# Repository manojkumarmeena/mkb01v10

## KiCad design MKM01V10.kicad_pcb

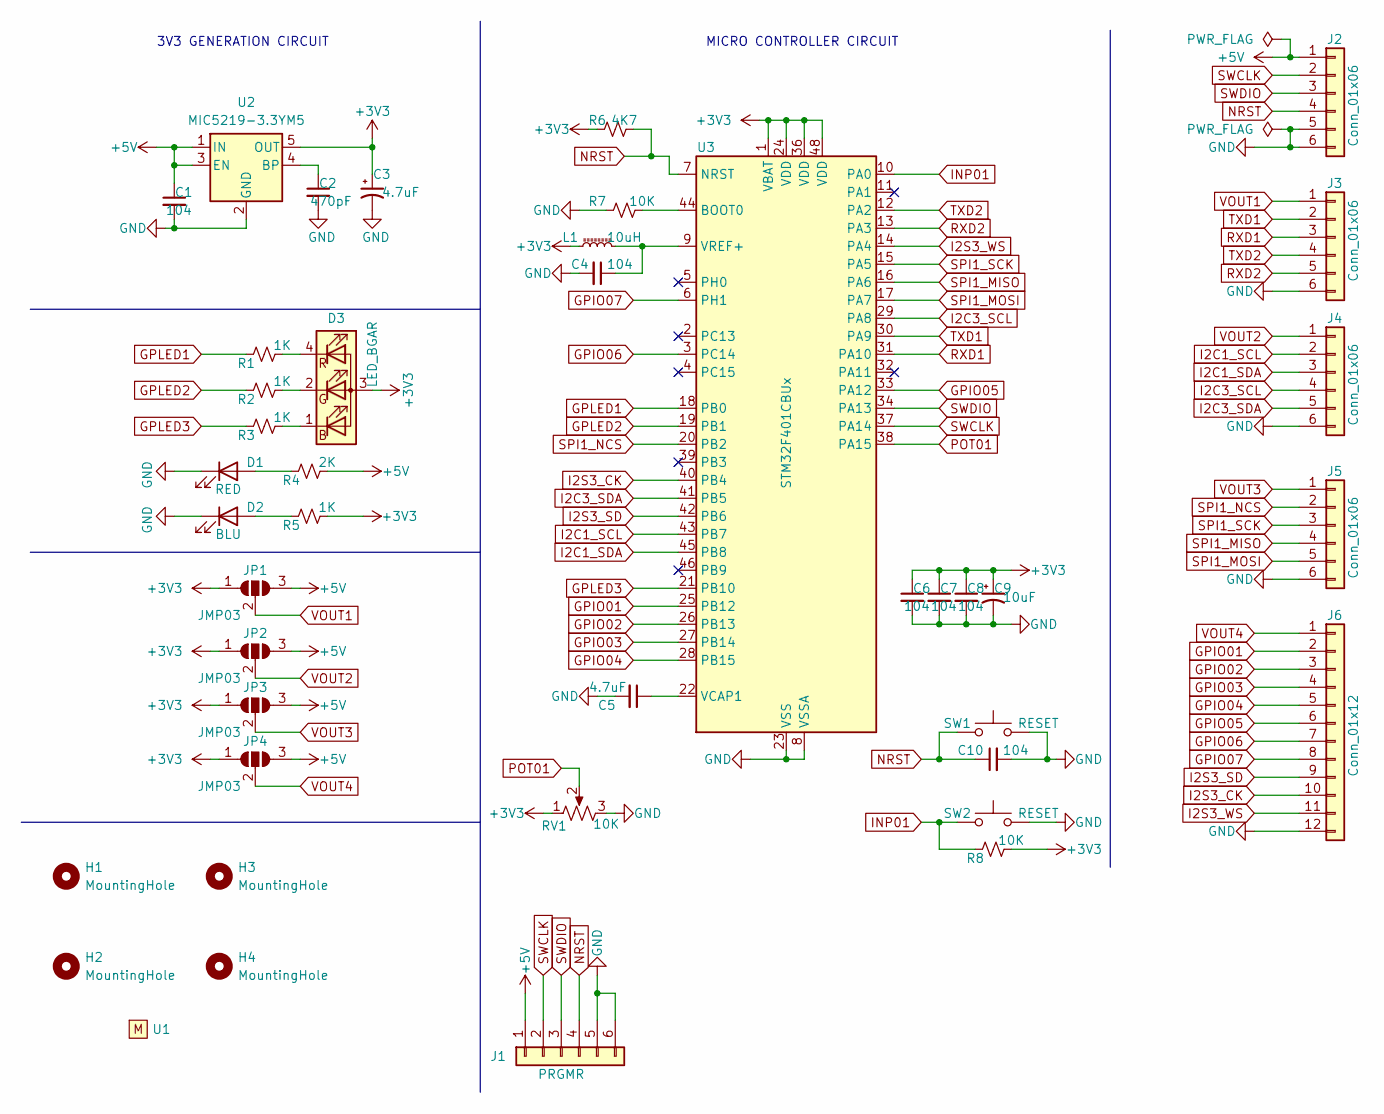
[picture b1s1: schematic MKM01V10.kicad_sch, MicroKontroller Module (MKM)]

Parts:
C1, C4, C6, C7, C8, C10: 104; C_0603_1608Metric_Pad1.08x0.95mm_HandSolder; PartNo C0603C104J5RACAUTO
C2: 470pF; C_0603_1608Metric_Pad1.08x0.95mm_HandSolder; PartNo C0603C471J5GACAUTO
C3: 4.7uF; CP_EIA-3216-18_Kemet-A; PartNo T495A225K016ATA6K5
C5: 4.7uF; C_1206_3216Metric_Pad1.33x1.80mm_HandSolder; PartNo C1206C475M5PACTU
C9: 10uF; CP_EIA-3216-18_Kemet-A; PartNo T491A106K016AG
D1: RED; LED_0603_1608Metric_Pad1.05x0.95mm_HandSolder
D2: BLU; LED_0603_1608Metric_Pad1.05x0.95mm_HandSolder
D3: LED_BGAR; LED_D5.0mm-4_RGB
H1, H2, H3, H4: MountingHole; MountingHole_3.2mm_M3
J1: PRGMR; PinHeader_1x06_P1.00mm_Vertical
J2: Conn_01x06; USB_Micro-B_Amphenol_10118194_Horizontal
J3, J4, J5: Conn_01x06; Hirose_DF13-06P-1.25DSA_1x06_P1.25mm_Vertical
J6: Conn_01x12; Hirose_DF13-12P-1.25DSA_1x12_P1.25mm_Vertical
JP1, JP2, JP3, JP4: JMP03; SolderJumper-3_P1.3mm_Open_Pad1.0x1.5mm
L1: 10uH; L_0603_1608Metric; PartNo FCM1608KF-601T05
R1, R2, R3, R5: 1K; R_0603_1608Metric_Pad0.98x0.95mm_HandSolder
R4: 2K; R_0603_1608Metric_Pad0.98x0.95mm_HandSolder
R6: 4K7; R_0603_1608Metric_Pad0.98x0.95mm_HandSolder; PartNo CRCW06034K70FKEAHP
R7: 10K; R_0603_1608Metric_Pad0.98x0.95mm_HandSolder; PartNo CRCW060310K0FKEAHP
R8: 10K; R_0603_1608Metric_Pad0.98x0.95mm_HandSolder
RV1: 10K; Potentiometer_ACP_CA6-H2,5_Horizontal
SW1, SW2: RESET; SW_SPST_B3U-1000P
U1: MKM-LOGON-V10; MKMLOGO-P
U2: MIC5219-3.3YM5; SOT-23-5; PartNo MIC5219-3.3YM5
U3: STM32F401CBUx; QFN-48-1EP_7x7mm_P0.5mm_EP5.6x5.6mm

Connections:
+3V3: C3.1, C6.1, C7.1, C8.1, C9.1, D3.3 (A), JP1.1 (A), JP2.1 (A), JP3.1 (A), JP4.1 (A), L1.1, R5.2, R6.2, R8.2, RV1.1, U2.5 (OUT), U3.1 (VBAT), U3.24 (VDD), U3.36 (VDD), U3.48 (VDD)
+5V: C1.1, J1.1, J2.1, JP1.3 (B), JP2.3 (B), JP3.3 (B), JP4.3 (B), R4.2, U2.1 (IN), U2.3 (EN)
BOOT: R7.2, U3.44 (BOOT0)
GND: C1.2, C2.2, C3.2, C4.2, C5.2, C6.2, C7.2, C8.2, C9.2, C10.2, D1.1 (K), D2.1 (K), J1.5, J1.6, J2.5, J2.6, J3.6, J4.6, J5.6, J6.12, R7.1, RV1.3, SW1.3 (B), SW1.4 (B), SW2.3 (B), SW2.4 (B), U2.2 (GND), U3.8 (VSSA), U3.23 (VSS), U3.35 (VSS), U3.47 (VSS), U3.49 (VSS)
GPIO01: J6.2, U3.25 (PB12)
GPIO02: J6.3, U3.26 (PB13)
GPIO03: J6.4, U3.27 (PB14)
GPIO04: J6.5, U3.28 (PB15)
GPIO05: J6.6, U3.33 (PA12)
GPIO06: J6.7, U3.3 (PC14)
GPIO07: J6.8, U3.6 (PH1)
GPLED1: R1.1, U3.18 (PB0)
GPLED2: R2.1, U3.19 (PB1)
GPLED3: R3.1, U3.21 (PB10)
I2C1_SCL: J4.2, U3.43 (PB7)
I2C1_SDA: J4.3, U3.45 (PB8)
I2C3_SCL: J4.4, U3.29 (PA8)
I2C3_SDA: J4.5, U3.41 (PB5)
I2S3_CK: J6.10, U3.40 (PB4)
I2S3_SD: J6.9, U3.42 (PB6)
I2S3_WS: J6.11, U3.14 (PA4)
INP01: R8.1, SW2.1 (A), SW2.2 (A), U3.10 (PA0)
NRST: C10.1, J1.4, J2.4, R6.1, SW1.1 (A), SW1.2 (A), U3.7 (NRST)
unnamed: D1.2 (A), R4.1
unnamed: D2.2 (A), R5.1
unnamed: D3.1 (BK), R3.2
unnamed: D3.2 (GK), R2.2
unnamed: D3.4 (RK), R1.2
unnamed: C2.1, U2.4 (BP)
unnamed: C5.1, U3.22 (VCAP1)
unnamed: C4.1, L1.2, U3.9 (VREF+)
POT01: RV1.2, U3.38 (PA15)
RXD1: J3.3, U3.31 (PA10)
RXD2: J3.5, U3.13 (PA3)
SPI1_MISO: J5.4, U3.16 (PA6)
SPI1_MOSI: J5.5, U3.17 (PA7)
SPI1_NCS: J5.2, U3.20 (PB2)
SPI1_SCK: J5.3, U3.15 (PA5)
SWCLK: J1.2, J2.2, U3.37 (PA14)
SWDIO: J1.3, J2.3, U3.34 (PA13)
TXD1: J3.2, U3.30 (PA9)
TXD2: J3.4, U3.12 (PA2)
VOUT1: J3.1, JP1.2 (C)
VOUT2: J4.1, JP2.2 (C)
VOUT3: J5.1, JP3.2 (C)
VOUT4: J6.1, JP4.2 (C)

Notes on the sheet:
3V3 GENERATION CIRCUIT
MICRO CONTROLLER CIRCUIT

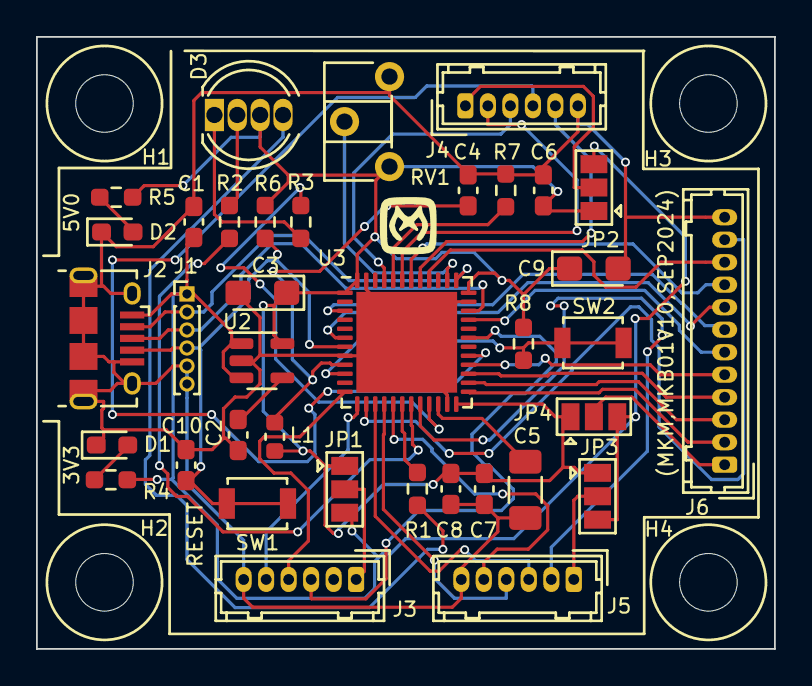
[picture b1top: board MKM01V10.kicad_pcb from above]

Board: 2 copper layers, 41.0 x 34.0 mm, 42 parts (0 on the bottom side), 46 nets.

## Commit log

2024-10-24 schematic files for stm32 development board
